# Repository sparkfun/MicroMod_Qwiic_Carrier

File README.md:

SparkFun MicroMod Qwiic Carrier Board
========================================

<table class="table table-hover table-striped table-bordered">
    <tr align="center">
      <td></td>
      <td></td>
    </tr>
    <tr align="center">
      <td><a href="https://www.sparkfun.com/products/17723">SparkFun Qwiic Carrier - Single</a></td>
      <td><a href="https://www.sparkfun.com/products/17724">SparkFun Qwiic Carrier - Double</a></td>
    </tr>
</table>

The MicroMod Qwiic Carrier Board for the [SparkFun MicroMod Ecosystem](https://www.sparkfun.com/micromod) can be used to rapidly prototype with other Qwiic devices. The MicroMod M.2 socket provides users the freedom to experiment with any processor board in the MicroMod ecosystem. This board also features two Qwiic connectors and 4-40 screw inserts to connect and mount Qwiic devices.

Repository Contents
-------------------
* **/Hardware** - Eagle design files (.brd, .sch)

Documentation
--------------
* **[Hookup Guide](https://learn.sparkfun.com/tutorials/1596)** - Basic hookup guide for the MicroMod Qwiic Carrier Board.

Product Versions
----------------
* [DEV-17723](https://www.sparkfun.com/products/17723) - Single
* [DEV-17724](https://www.sparkfun.com/products/17724) - Double

License Information
-------------------

This product is _**open source**_! 

Please review the LICENSE.md file for license information. 

If you have any questions or concerns on licensing, please contact technical support on our [SparkFun forums](https://forum.sparkfun.com/viewforum.php?f=152).

Distributed as-is; no warranty is given.

- Your friends at SparkFun.

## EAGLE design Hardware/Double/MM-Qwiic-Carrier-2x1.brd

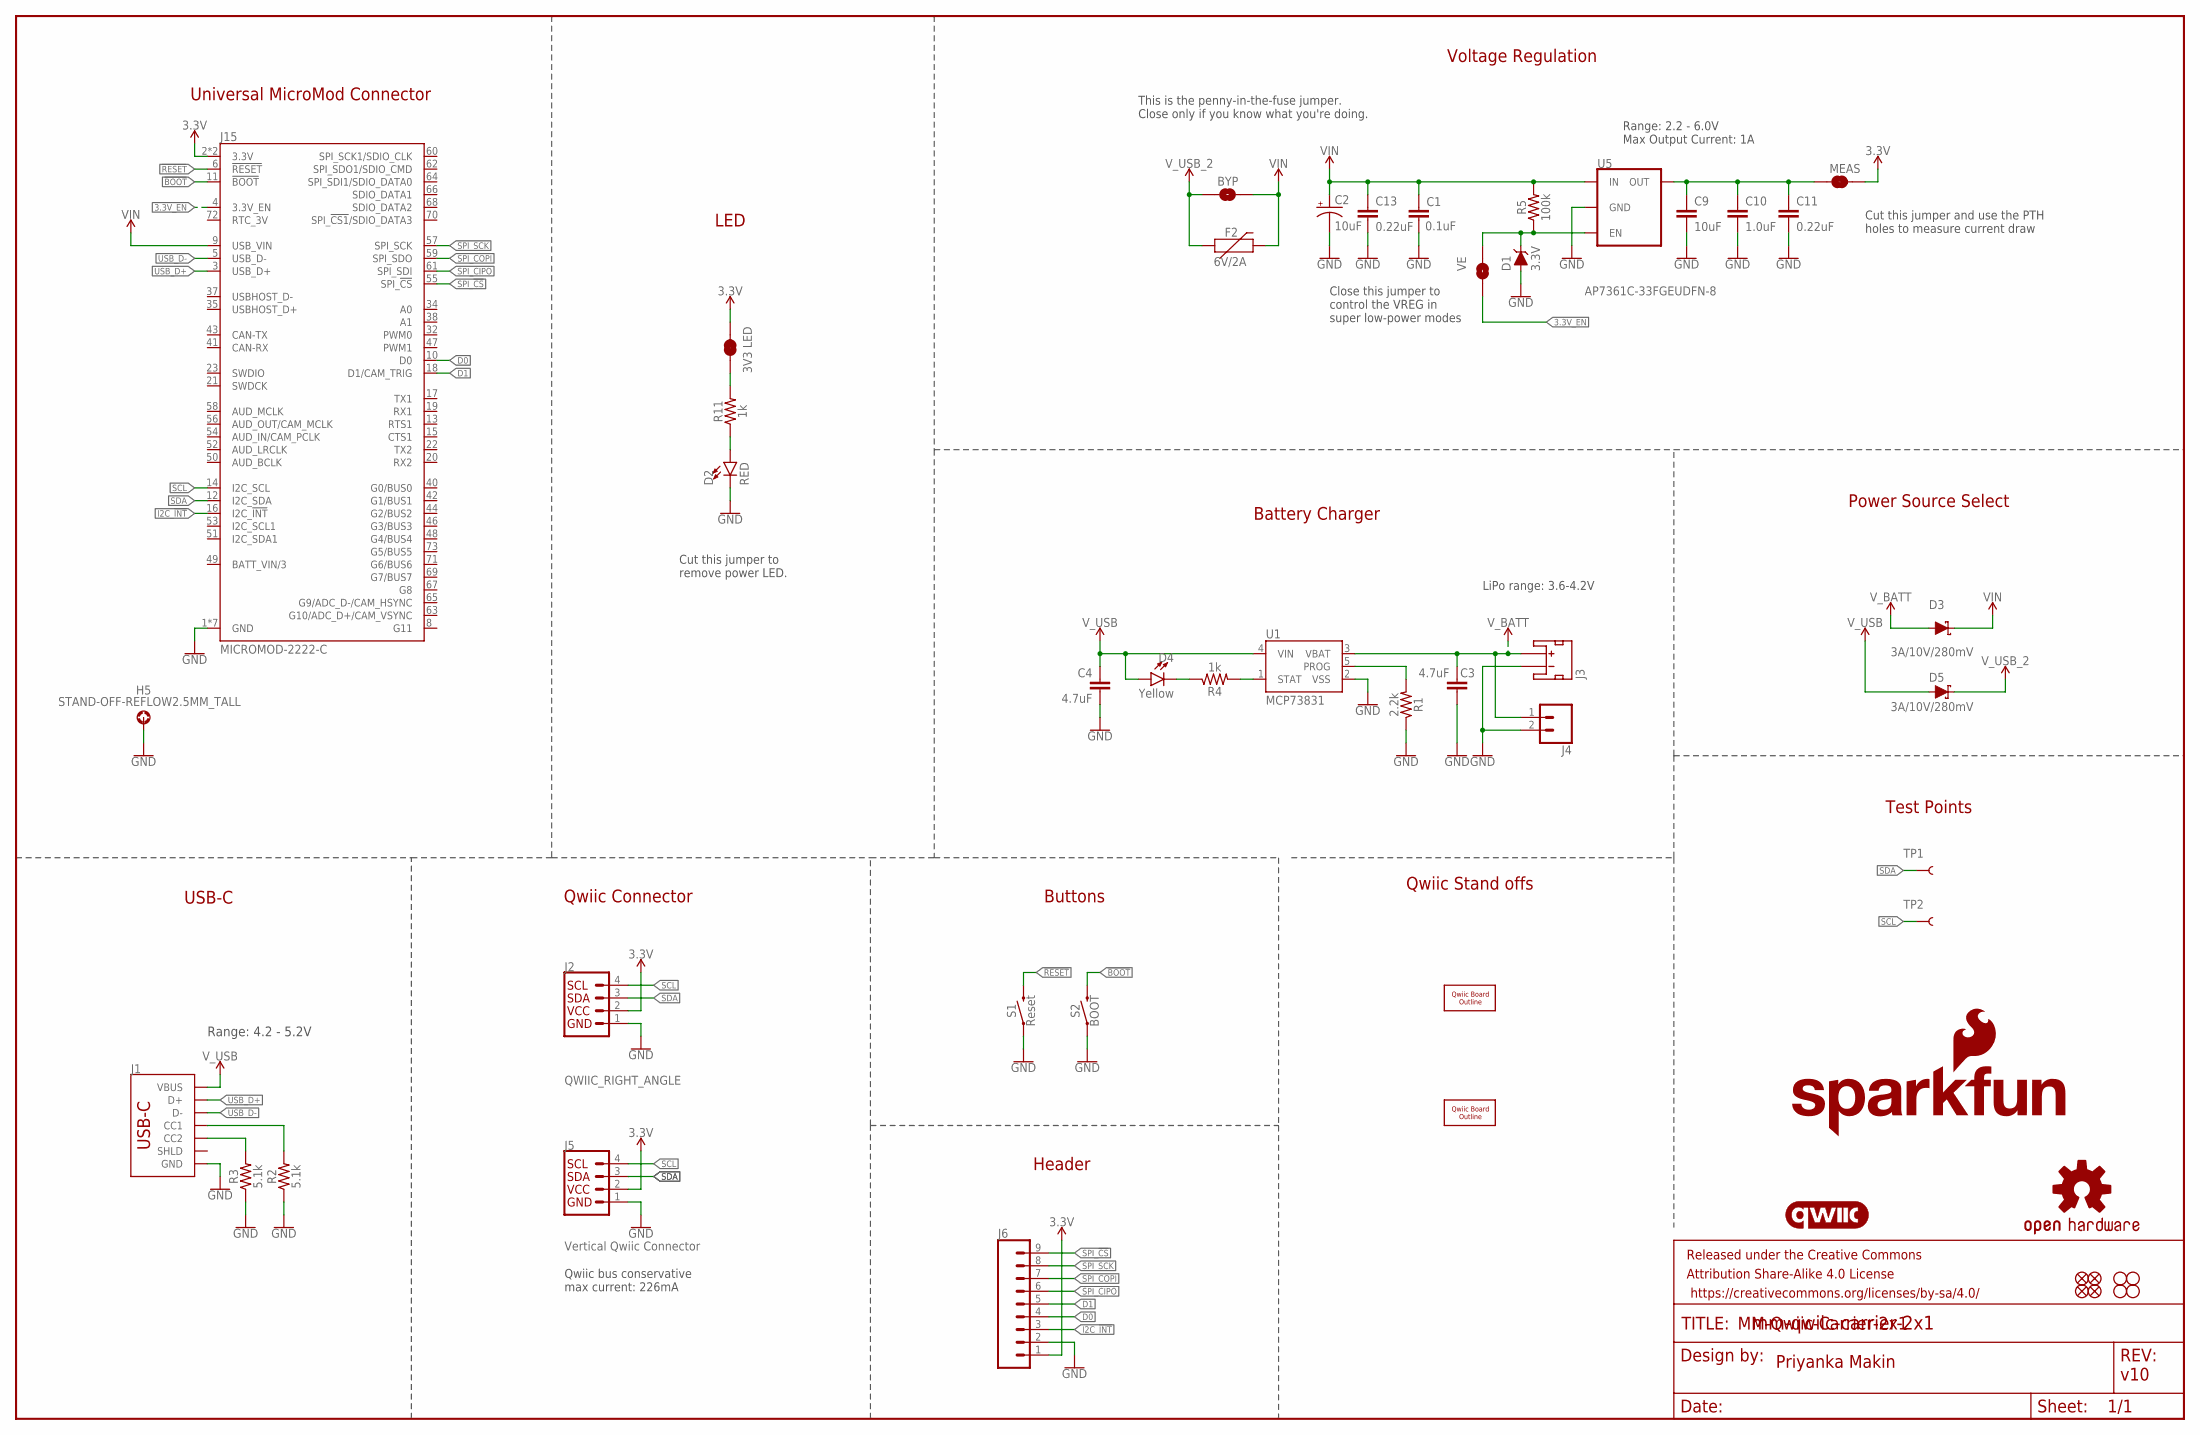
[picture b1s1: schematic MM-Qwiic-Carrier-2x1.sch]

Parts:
BYP: JUMPER-SMT_2_NO_SILK; SMT-JUMPER_2_NO_SILK
C1: 0.1uF; 0603
C2: 10uF; EIA3216
C3, C4: 4.7uF; 0603
C9: 10uF; 0603
C10: 1.0uF; 0603
C11, C13: 0.22uF; 0603
D1: 3.3V; SOD-323
D2: RED; LED-0603
D3, D5: 3A/10V/280mV; SOD-323
D4: Yellow; LED-0603
F2: 6V/2A; 1210
FD1, FD2, FD3, FD4: FIDUCIALUFIDUCIAL; FIDUCIAL-MICRO
FRAME1: FRAME-LEDGER; CREATIVE_COMMONS
H1, H2, H3, H4: STAND-OFF
H5: STAND-OFF-REFLOW2.5MM_TALL; STAND-OFF-REFLOW-M2.5
J1: USB_C_2-LAYER_PADS; USB-C-16P-2LAYER-PADS
J2: QWIIC_RIGHT_ANGLE; JST04_1MM_RA
J3: JST_2MM_MALE; JST-2-SMD
J4: CONN_021X02_NO_SILK; 1X02_NO_SILK
J5: Vertical Qwiic Connector; JST04_1MM_VERT
J6: CONN_09NO_SILK; 1X09_NO_SILK
J15: MICROMOD-2222-C; M.2-CONNECTOR-E
JP4: 3V3 LED; SMT-JUMPER_2_NC_TRACE_SILK
JP6: VE; SMT-JUMPER_2_NO_SILK
LOGO1: SFE_LOGO_NAME_FLAME.2_INCH; SFE_LOGO_NAME_FLAME_.2
LOGO2: QWIIC_LOGO_CONNECTOR; QWIIC_5.5MM
LOGO3: OSHW-LOGOM; OSHW-LOGO-M
MEAS: JUMPER-COMBO_2_NC_TRACE; COMBO-JUMPER_2_NC_TRACE
R1: 2.2k; 0603
R2, R3: 5.1k; 0603
R4, R11: 1k; 0603
R5: 100k; 0603
S1: Reset; TACTILE_SWITCH_SMD_5.2MM
S2: BOOT; TACTILE_SWITCH_SMD_5.2MM
TP1, TP2: TEST-POINT3X5; PAD.03X.05
U1: MCP73831; SOT23-5
U5: AP7361C-33FGEUDFN-8; UDFN-8
U$2, U$5: QWIIC_BOARD_OUTLINESTANDOFF; QWIIC_BOARD_MOUNT_SMD_STANDOFFS

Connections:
3.3V: J2.2, J5.2, J6.1, J15.2 (3.3V), J15.74 (3.3V), JP4.2, MEAS.2, MEAS.4 (2)
3.3V_EN: J15.4 (3.3V_EN), JP6.1
!BOOT!: J15.11 (!BOOT!), S2.3 (2), S2.4 (2)
!RESET!: J15.6 (!RESET!), S1.3 (2), S1.4 (2)
D0: J6.4, J15.10 (D0)
D1: J6.5, J15.18 (D1/CAM_TRIG)
GND: C1.2, C2.-, C3.2, C4.2, C9.2, C10.2, C11.2, C13.2, D1.A, D2.C, H5.1, J1.GND, J1.GND2 (GND), J2.1, J3.1 (-), J4.2, J5.1, J6.2, J15.1 (GND), J15.7 (GND), J15.33 (GND), J15.36 (GND), J15.39 (GND), J15.45 (GND), J15.75 (GND), R1.1, R2.1, R3.1, S1.1, S1.2 (1), S2.1, S2.2 (1), U1.2 (VSS), U5.4 (GND), U5.EP (GND)
I2C_!INT!: J6.3, J15.16 (I2C_!INT!)
unnamed: C9.1, C10.1, C11.1, MEAS.1, MEAS.3 (1), U5.1 (OUT)
unnamed: R1.2, U1.5 (PROG)
unnamed: D4.C, R4.1
unnamed: JP4.1, R11.2
unnamed: D2.A, R11.1
unnamed: R4.2, U1.1 (STAT)
unnamed: J1.A5 (CC1), R2.2
unnamed: J1.B5 (CC2), R3.2
SCL: J2.4, J5.4, J15.14 (I2C_SCL), TP2.P$1
SDA: J2.3, J5.3, J15.12 (I2C_SDA), TP1.P$1
SPI_!CS!: J6.9, J15.55 (SPI_!CS!)
SPI_CIPO: J6.6, J15.61 (SPI_SDI)
SPI_COPI: J6.7, J15.59 (SPI_SDO)
SPI_SCK: J6.8, J15.57 (SPI_SCK)
USB_D+: J1.A6 (D+), J1.B6 (D+), J15.3 (USB_D+)
USB_D-: J1.A7 (D-), J1.B7 (D-), J15.5 (USB_D-)
VIN: BYP.2, C1.1, C2.+, C13.1, D3.C, F2.2, J15.9 (USB_VIN), R5.2, U5.8 (IN)
VREG_EN: D1.C, JP6.2, R5.1, U5.5 (EN)
V_BATT: C3.1, D3.A, J3.2 (+), J4.1, U1.3 (VBAT)
V_USB: C4.1, D4.A, D5.A, J1.VBUS1 (VBUS), J1.VBUS2 (VBUS), U1.4 (VIN)
V_USB_2: BYP.1, D5.C, F2.1

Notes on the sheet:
USB-C
Universal MicroMod Connector
Priyanka Makin
MM-Qwiic-Carrier-2x1
LED
v10
Cut this jumper to remove power LED.
Range: 4.2 - 5.2V
Voltage Regulation
Range: 2.2 - 6.0V Max Output Current: 1A
Close this jumper to control the VREG in super low-power modes
This is the penny-in-the-fuse jumper. Close only if you know what you're doing.
Qwiic Connector
Buttons
Battery Charger
Qwiic Stand offs
Power Source Select
Test Points
Qwiic bus conservative max current: 226mA
Header
Cut this jumper and use the PTH holes to measure current draw
LiPo range: 3.6-4.2V

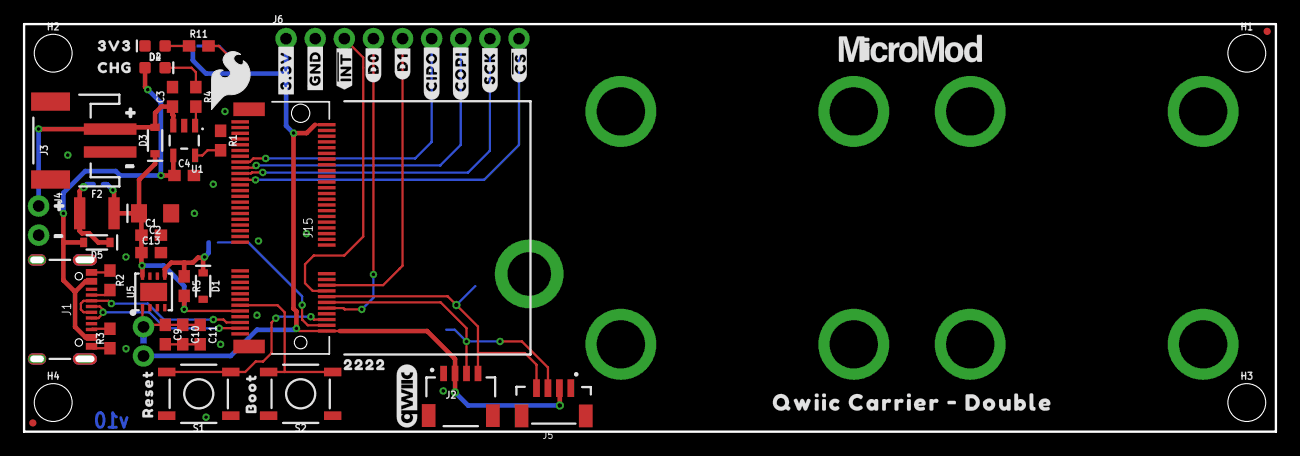
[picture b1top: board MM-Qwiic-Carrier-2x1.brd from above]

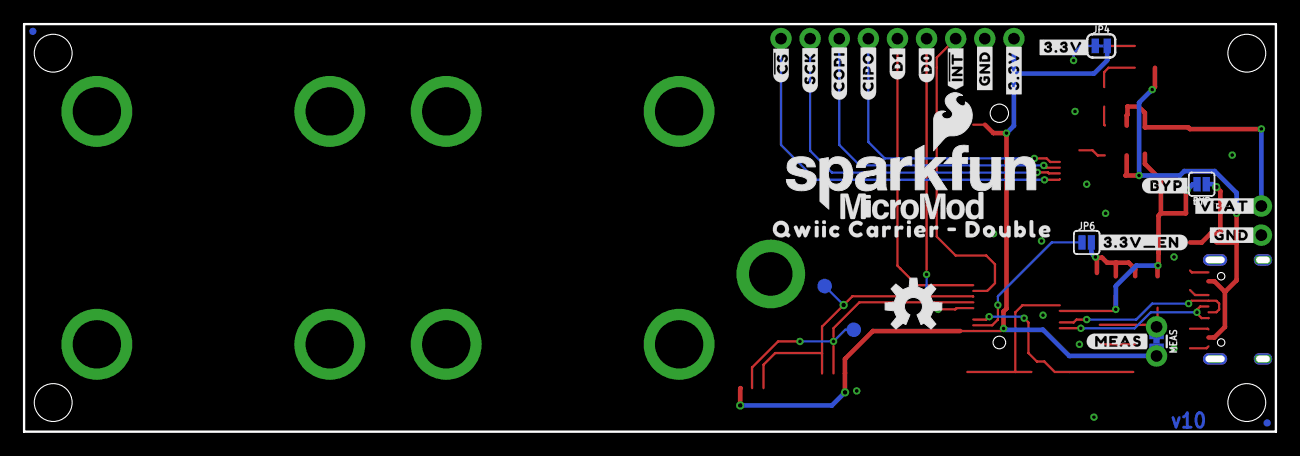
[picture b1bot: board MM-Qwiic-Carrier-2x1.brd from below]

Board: 2 copper layers, 109.2 x 35.6 mm, 90 parts (27 on the bottom side), 29 nets.

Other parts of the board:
U$1: #3#3V_EN#0
U$3: 3V30
U$4: CHG0
U$6, U$35, U$38: #3#3V#0
U$7: #BYP#0
U$8, U$14, U$33: #GND#0
U$9: #MEAS#0
U$10, U$13: QWIIC_CARRIER_#_DOUBLE0
U$11, U$32, U$36, U$37: #0
U$12: #VBAT#0
U$15, U$16: ##INT##0
U$17, U$18: #D0#0
U$20, U$21: #D1#0
U$22, U$23: #CIPO#0
U$24, U$25: #COPI#0
U$26, U$27: #SCK#0
U$28, U$29: ##CS##0
U$30: RESET0
U$31: BOOT0
U$34: 22220
U$44: SFE_LOGO_FLAME_.2
U$67, U$68: MICROMOD_LOGO_.5

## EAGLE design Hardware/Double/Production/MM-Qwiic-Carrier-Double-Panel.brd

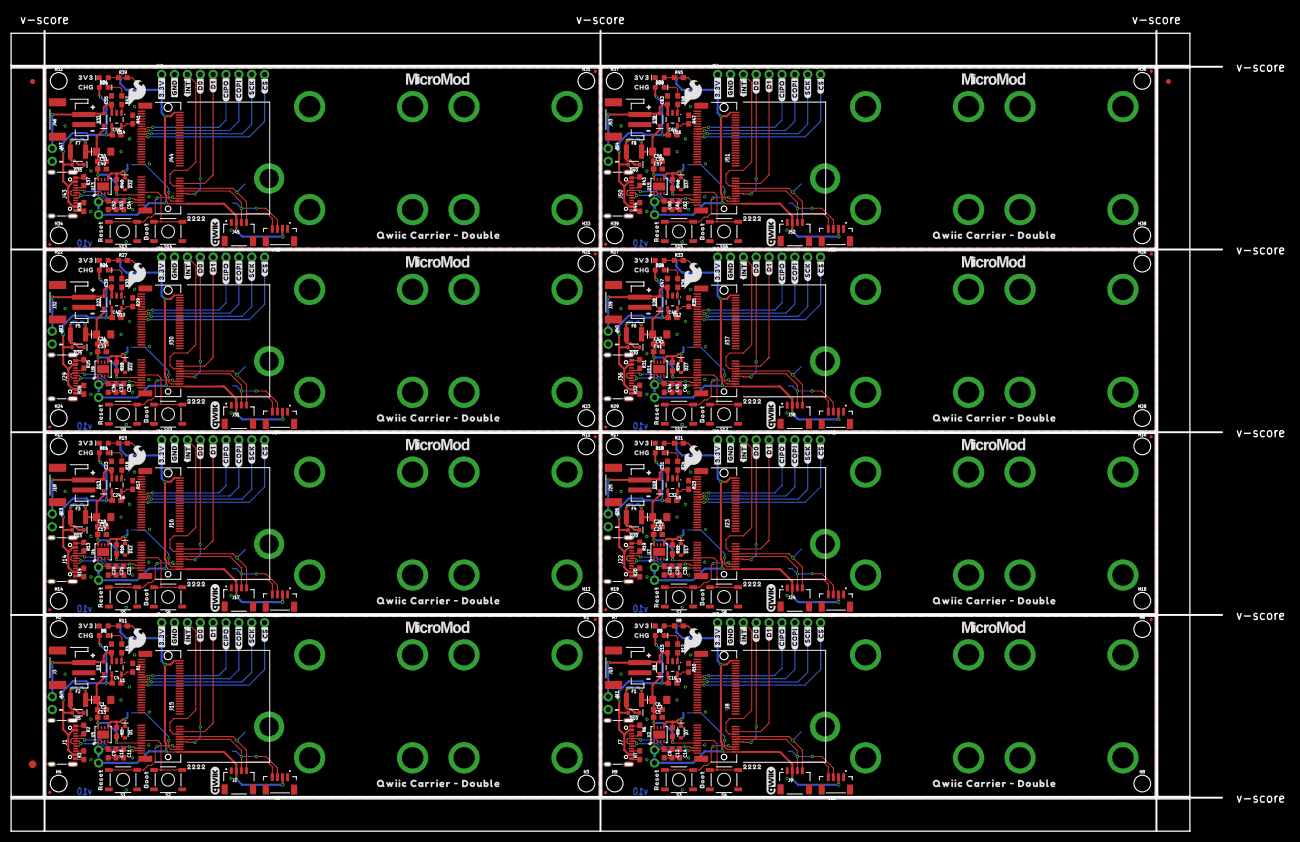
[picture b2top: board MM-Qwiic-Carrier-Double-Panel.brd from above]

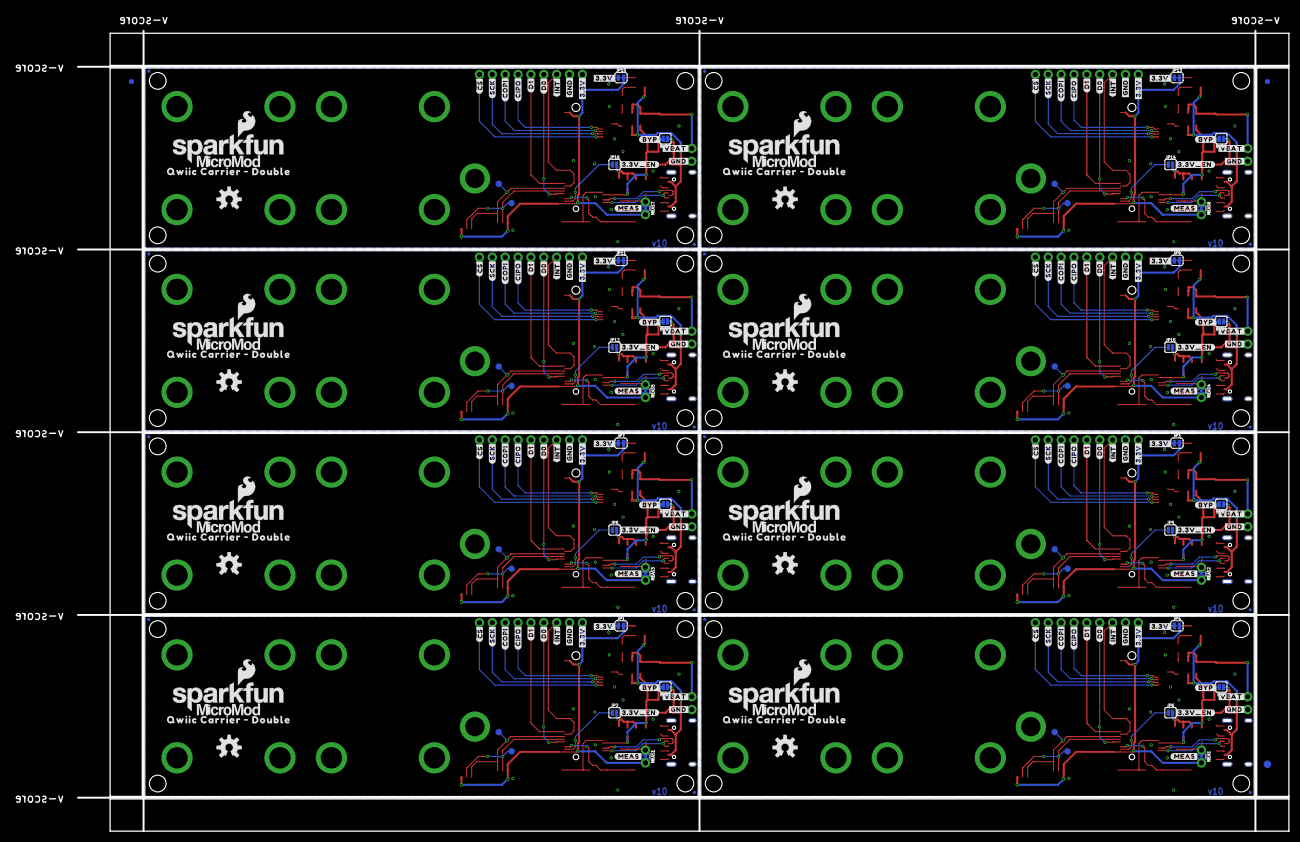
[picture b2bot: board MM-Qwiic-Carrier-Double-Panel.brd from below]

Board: 2 copper layers, 239.0 x 158.0 mm, 718 parts (219 on the bottom side), 232 nets.

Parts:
BYP, BYP1, BYP2, BYP3, BYP4, BYP5, BYP6, BYP7: JUMPER-SMT_2_NO_SILK; SMT-JUMPER_2_NO_SILK
C1, C6, C18, C26, C34, C42, C50, C58: 0.1uF; 0603
C2, C7, C19, C27, C35, C43, C51, C59: 10uF; EIA3216
C3, C4, C15, C16, C23, C24, C31, C32, C39, C40, C47, C48, C55, C56, C63, C64: 4.7uF; 0603
C5, C11, C13, C14, C17, C22, C25, C30, C33, C38, C41, C46, C49, C54, C57, C62: 0.22uF; 0603
C8, C9, C20, C28, C36, C44, C52, C60: 10uF; 0603
C10, C12, C21, C29, C37, C45, C53, C61: 1.0uF; 0603
D1, D7, D12, D17, D22, D27, D32, D37: 3.3V; SOD-323
D2, D6, D11, D16, D21, D26, D31, D36: RED; LED-0603
D3, D5, D8, D10, D13, D15, D18, D20, D23, D25, D28, D30, D33, D35, D38, D40: 3A/10V/280mV; SOD-323
D4, D9, D14, D19, D24, D29, D34, D39: Yellow; LED-0603
E$1, E$2, E$3, E$4: FIDUCIAL-1X2
E$5, E$6: FIDUCIAL-1.5X3
F1, F2, F3, F4, F5, F6, F7, F8: 6V/2A; 1210
FD1, FD2, FD3, FD4, FD5, FD6, FD7, FD8, FD9, FD10, FD11, FD12, FD13, FD14, FD15, FD16, FD17, FD18, FD19, FD20, FD21, FD22, FD23, FD24, FD25, FD26, FD27, FD28, FD29, FD30, FD31, FD32: FIDUCIALUFIDUCIAL; FIDUCIAL-MICRO
H1, H2, H3, H4, H6, H7, H8, H9, H11, H12, H13, H14, H16, H17, H18, H19, H21, H22, H23, H24, H26, H27, H28, H29, H31, H32, H33, H34, H36, H37, H38, H39: STAND-OFF
H5, H10, H15, H20, H25, H30, H35, H40: STAND-OFF-REFLOW2.5MM_TALL; STAND-OFF-REFLOW-M2.5
J1, J7, J14, J22, J29, J36, J43, J50: USB-C-16P-2LAYER-PADS
J2, J9, J17, J24, J31, J38, J45, J52: QWIIC_RIGHT_ANGLE; JST04_1MM_RA
J3, J10, J18, J25, J32, J39, J46, J53: JST-2-SMD
J4, J11, J19, J26, J33, J40, J47, J54: 1X02_NO_SILK
J5, J12, J20, J27, J34, J41, J48, J55: Vertical Qwiic Connector; JST04_1MM_VERT
J6, J13, J21, J28, J35, J42, J49, J56: 1X09_NO_SILK
J8, J15, J16, J23, J30, J37, J44, J51: MICROMOD-2222-C; M.2-CONNECTOR-E
JP1, JP3, JP4, JP7, JP9, JP11, JP13, JP15: 3V3 LED; SMT-JUMPER_2_NC_TRACE_SILK
JP2, JP5, JP6, JP8, JP10, JP12, JP14, JP16: VE; SMT-JUMPER_2_NO_SILK
LOGO1, LOGO6, LOGO9, LOGO12, LOGO15, LOGO18, LOGO21, LOGO24: SFE_LOGO_NAME_FLAME.2_INCH; SFE_LOGO_NAME_FLAME_.2
LOGO2, LOGO4, LOGO7, LOGO10, LOGO13, LOGO16, LOGO19, LOGO22: QWIIC_LOGO_CONNECTOR; QWIIC_5.5MM
LOGO3, LOGO5, LOGO8, LOGO11, LOGO14, LOGO17, LOGO20, LOGO23: OSHW-LOGOM; OSHW-LOGO-M
MEAS, MEAS1, MEAS2, MEAS3, MEAS4, MEAS5, MEAS6, MEAS7: COMBO-JUMPER_2_NC_TRACE
R1, R10, R17, R23, R29, R35, R41, R47: 2.2k; 0603
R2, R3, R6, R7, R13, R14, R19, R20, R25, R26, R31, R32, R37, R38, R43, R44: 5.1k; 0603
R4, R8, R11, R12, R15, R18, R21, R24, R27, R30, R33, R36, R39, R42, R45, R48: 1k; 0603
R5, R9, R16, R22, R28, R34, R40, R46: 100k; 0603
S1, S3, S5, S7, S9, S11, S13, S15: Reset; TACTILE_SWITCH_SMD_5.2MM
S2, S4, S6, S8, S10, S12, S14, S16: BOOT; TACTILE_SWITCH_SMD_5.2MM
TP1, TP2, TP3, TP4, TP5, TP6, TP7, TP8, TP9, TP10, TP11, TP12, TP13, TP14, TP15, TP16: TEST-POINT3X5; PAD.03X.05
U1, U3, U6, U8, U10, U12, U14, U16: MCP73831; SOT23-5
U2, U4, U5, U7, U9, U11, U13, U15: AP7361C-33FGEUDFN-8; UDFN-8
U$1, U$48, U$90, U$130, U$170, U$210, U$250, U$290: #3#3V_EN#0
U$2, U$5, U$46, U$78, U$88, U$118, U$128, U$158, U$168, U$198, U$208, U$238, U$248, U$278, U$288, U$318: QWIIC_BOARD_OUTLINESTANDOFF; QWIIC_BOARD_MOUNT_SMD_STANDOFFS
U$3, U$47, U$89, U$129, U$169, U$209, U$249, U$289: 3V30
U$4, U$41, U$84, U$124, U$164, U$204, U$244, U$284: CHG0
U$6, U$35, U$38, U$42, U$72, U$73, U$85, U$112, U$113, U$125, U$152, U$153, U$165, U$192, U$193, U$205, U$232, U$233, U$245, U$272, U$273, U$285, U$312, U$313: #3#3V#0
U$7, U$43, U$86, U$126, U$166, U$206, U$246, U$286: #BYP#0
U$8, U$14, U$33, U$49, U$50, U$58, U$91, U$92, U$100, U$131, U$132, U$140, U$171, U$172, U$180, U$211, U$212, U$220, U$251, U$252, U$260, U$291, U$292, U$300: #GND#0
U$9, U$45, U$87, U$127, U$167, U$207, U$247, U$287: #MEAS#0
U$10, U$13, U$79, U$80, U$119, U$120, U$159, U$160, U$199, U$200, U$239, U$240, U$279, U$280, U$319, U$320: QWIIC_CARRIER_#_DOUBLE0
U$11, U$32, U$36, U$37, U$59, U$60, U$61, U$62, U$101, U$102, U$103, U$104, U$141, U$142, U$143, U$144, U$181, U$182, U$183, U$184, U$221, U$222, U$223, U$224, U$261, U$262, U$263, U$264, U$301, U$302, U$303, U$304: #0
U$12, U$57, U$99, U$139, U$179, U$219, U$259, U$299: #VBAT#0
U$15, U$16, U$76, U$77, U$116, U$117, U$156, U$157, U$196, U$197, U$236, U$237, U$276, U$277, U$316, U$317: ##INT##0
U$17, U$18, U$63, U$64, U$105, U$106, U$145, U$146, U$185, U$186, U$225, U$226, U$265, U$266, U$305, U$306: #D0#0
U$19, U$44, U$81, U$121, U$161, U$201, U$241, U$281: SFE_LOGO_FLAME_.2
U$20, U$21, U$65, U$66, U$107, U$108, U$147, U$148, U$187, U$188, U$227, U$228, U$267, U$268, U$307, U$308: #D1#0
U$22, U$23, U$51, U$52, U$93, U$94, U$133, U$134, U$173, U$174, U$213, U$214, U$253, U$254, U$293, U$294: #CIPO#0
U$24, U$25, U$53, U$54, U$95, U$96, U$135, U$136, U$175, U$176, U$215, U$216, U$255, U$256, U$295, U$296: #COPI#0
U$26, U$27, U$55, U$56, U$97, U$98, U$137, U$138, U$177, U$178, U$217, U$218, U$257, U$258, U$297, U$298: #SCK#0
U$28, U$29, U$74, U$75, U$114, U$115, U$154, U$155, U$194, U$195, U$234, U$235, U$274, U$275, U$314, U$315: ##CS##0
U$30, U$69, U$109, U$149, U$189, U$229, U$269, U$309: RESET0
U$31, U$70, U$110, U$150, U$190, U$230, U$270, U$310: BOOT0
U$34, U$71, U$111, U$151, U$191, U$231, U$271, U$311: 22220
U$39, U$40, U$67, U$68, U$82, U$83, U$122, U$123, U$162, U$163, U$202, U$203, U$242, U$243, U$282, U$283: MICROMOD_LOGO_.5

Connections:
3.3V: J2.2, J5.2, J6.1, J15.2, J15.74, JP4.2, MEAS.2, MEAS.4
3.3V1: J8.2, J8.74, J9.2, J12.2, J13.1, JP1.2, MEAS1.2, MEAS1.4
3.3V2: J16.2, J16.74, J17.2, J20.2, J21.1, JP3.2, MEAS2.2, MEAS2.4
3.3V3: J23.2, J23.74, J24.2, J27.2, J28.1, JP7.2, MEAS3.2, MEAS3.4
3.3V4: J30.2, J30.74, J31.2, J34.2, J35.1, JP9.2, MEAS4.2, MEAS4.4
3.3V5: J37.2, J37.74, J38.2, J41.2, J42.1, JP11.2, MEAS5.2, MEAS5.4
3.3V6: J44.2, J44.74, J45.2, J48.2, J49.1, JP13.2, MEAS6.2, MEAS6.4
3.3V7: J51.2, J51.74, J52.2, J55.2, J56.1, JP15.2, MEAS7.2, MEAS7.4
3.3V_EN: J15.4, JP6.1
3.3V_EN1: J8.4, JP2.1
3.3V_EN2: J16.4, JP5.1
3.3V_EN3: J23.4, JP8.1
3.3V_EN4: J30.4, JP10.1
3.3V_EN5: J37.4, JP12.1
3.3V_EN6: J44.4, JP14.1
3.3V_EN7: J51.4, JP16.1
!BOOT!: J15.11, S2.3, S2.4
!BOOT!1: J8.11, S4.3, S4.4
!BOOT!2: J16.11, S6.3, S6.4
!BOOT!3: J23.11, S8.3, S8.4
!BOOT!4: J30.11, S10.3, S10.4
!BOOT!5: J37.11, S12.3, S12.4
!BOOT!6: J44.11, S14.3, S14.4
!BOOT!7: J51.11, S16.3, S16.4
!RESET!: J15.6, S1.3, S1.4
!RESET!1: J8.6, S3.3, S3.4
!RESET!2: J16.6, S5.3, S5.4
!RESET!3: J23.6, S7.3, S7.4
!RESET!4: J30.6, S9.3, S9.4
!RESET!5: J37.6, S11.3, S11.4
!RESET!6: J44.6, S13.3, S13.4
!RESET!7: J51.6, S15.3, S15.4
D0: J6.4, J15.10
D1: J6.5, J15.18
D2: J8.10, J13.4
D3: J8.18, J13.5
D4: J16.10, J21.4
D5: J16.18, J21.5
D6: J23.10, J28.4
D7: J23.18, J28.5
D8: J30.10, J35.4
D9: J30.18, J35.5
D10: J37.10, J42.4
D11: J37.18, J42.5
D12: J44.10, J49.4
D13: J44.18, J49.5
D14: J51.10, J56.4
D15: J51.18, J56.5
GND: C1.2, C2.-, C3.2, C4.2, C9.2, C10.2, C11.2, C13.2, D1.A, D2.C, H5.1, J1.GND, J1.GND2, J2.1, J3.1, J4.2, J5.1, J6.2, J15.1, J15.7, J15.33, J15.36, J15.39, J15.45, J15.75, R1.1, R2.1, R3.1, S1.1, S1.2, S2.1, S2.2, U1.2, U5.4, U5.EP
GND1: C5.2, C6.2, C7.-, C8.2, C12.2, C14.2, C15.2, C16.2, D6.C, D7.A, H10.1, J7.GND, J7.GND2, J8.1, J8.7, J8.33, J8.36, J8.39, J8.45, J8.75, J9.1, J10.1, J11.2, J12.1, J13.2, R6.1, R7.1, R10.1, S3.1, S3.2, S4.1, S4.2, U2.4, U2.EP, U3.2
GND2: C17.2, C18.2, C19.-, C20.2, C21.2, C22.2, C23.2, C24.2, D11.C, D12.A, H15.1, J14.GND, J14.GND2, J16.1, J16.7, J16.33, J16.36, J16.39, J16.45, J16.75, J17.1, J18.1, J19.2, J20.1, J21.2, R13.1, R14.1, R17.1, S5.1, S5.2, S6.1, S6.2, U4.4, U4.EP, U6.2
GND3: C25.2, C26.2, C27.-, C28.2, C29.2, C30.2, C31.2, C32.2, D16.C, D17.A, H20.1, J22.GND, J22.GND2, J23.1, J23.7, J23.33, J23.36, J23.39, J23.45, J23.75, J24.1, J25.1, J26.2, J27.1, J28.2, R19.1, R20.1, R23.1, S7.1, S7.2, S8.1, S8.2, U7.4, U7.EP, U8.2
GND4: C33.2, C34.2, C35.-, C36.2, C37.2, C38.2, C39.2, C40.2, D21.C, D22.A, H25.1, J29.GND, J29.GND2, J30.1, J30.7, J30.33, J30.36, J30.39, J30.45, J30.75, J31.1, J32.1, J33.2, J34.1, J35.2, R25.1, R26.1, R29.1, S9.1, S9.2, S10.1, S10.2, U9.4, U9.EP, U10.2
GND5: C41.2, C42.2, C43.-, C44.2, C45.2, C46.2, C47.2, C48.2, D26.C, D27.A, H30.1, J36.GND, J36.GND2, J37.1, J37.7, J37.33, J37.36, J37.39, J37.45, J37.75, J38.1, J39.1, J40.2, J41.1, J42.2, R31.1, R32.1, R35.1, S11.1, S11.2, S12.1, S12.2, U11.4, U11.EP, U12.2
GND6: C49.2, C50.2, C51.-, C52.2, C53.2, C54.2, C55.2, C56.2, D31.C, D32.A, H35.1, J43.GND, J43.GND2, J44.1, J44.7, J44.33, J44.36, J44.39, J44.45, J44.75, J45.1, J46.1, J47.2, J48.1, J49.2, R37.1, R38.1, R41.1, S13.1, S13.2, S14.1, S14.2, U13.4, U13.EP, U14.2
GND7: C57.2, C58.2, C59.-, C60.2, C61.2, C62.2, C63.2, C64.2, D36.C, D37.A, H40.1, J50.GND, J50.GND2, J51.1, J51.7, J51.33, J51.36, J51.39, J51.45, J51.75, J52.1, J53.1, J54.2, J55.1, J56.2, R43.1, R44.1, R47.1, S15.1, S15.2, S16.1, S16.2, U15.4, U15.EP, U16.2
I2C_!INT!: J6.3, J15.16
I2C_!INT!1: J8.16, J13.3
I2C_!INT!2: J16.16, J21.3
I2C_!INT!3: J23.16, J28.3
I2C_!INT!4: J30.16, J35.3
I2C_!INT!5: J37.16, J42.3
I2C_!INT!6: J44.16, J49.3
I2C_!INT!7: J51.16, J56.3
unnamed: C9.1, C10.1, C11.1, MEAS.1, MEAS.3, U5.1
unnamed: R1.2, U1.5
unnamed: D4.C, R4.1
unnamed: JP4.1, R11.2
unnamed: J7.A5, R6.2
unnamed: D2.A, R11.1
unnamed: J7.B5, R7.2
unnamed: R4.2, U1.1
unnamed: JP1.1, R8.2
unnamed: J1.A5, R2.2
unnamed: J1.B5, R3.2
unnamed: D6.A, R8.1
unnamed: C8.1, C12.1, C14.1, MEAS1.1, MEAS1.3, U2.1
unnamed: R10.2, U3.5
unnamed: D9.C, R12.1
unnamed: R12.2, U3.1
unnamed: J14.A5, R13.2
unnamed: J14.B5, R14.2
unnamed: JP3.1, R15.2
unnamed: D11.A, R15.1
unnamed: C20.1, C21.1, C22.1, MEAS2.1, MEAS2.3, U4.1
unnamed: R17.2, U6.5
unnamed: D14.C, R18.1
unnamed: R18.2, U6.1
unnamed: J22.A5, R19.2
unnamed: J22.B5, R20.2
unnamed: JP7.1, R21.2
unnamed: D16.A, R21.1
unnamed: C28.1, C29.1, C30.1, MEAS3.1, MEAS3.3, U7.1
unnamed: R23.2, U8.5
unnamed: D19.C, R24.1
unnamed: R24.2, U8.1
unnamed: J29.A5, R25.2
unnamed: J29.B5, R26.2
unnamed: JP9.1, R27.2
unnamed: D21.A, R27.1
unnamed: C36.1, C37.1, C38.1, MEAS4.1, MEAS4.3, U9.1
unnamed: R29.2, U10.5
unnamed: D24.C, R30.1
unnamed: R30.2, U10.1
unnamed: J36.A5, R31.2
unnamed: J36.B5, R32.2
unnamed: JP11.1, R33.2
unnamed: D26.A, R33.1
unnamed: C44.1, C45.1, C46.1, MEAS5.1, MEAS5.3, U11.1
unnamed: R35.2, U12.5
unnamed: D29.C, R36.1
unnamed: R36.2, U12.1
unnamed: J43.A5, R37.2
unnamed: J43.B5, R38.2
unnamed: JP13.1, R39.2
unnamed: D31.A, R39.1
unnamed: C52.1, C53.1, C54.1, MEAS6.1, MEAS6.3, U13.1
unnamed: R41.2, U14.5
unnamed: D34.C, R42.1
unnamed: R42.2, U14.1
unnamed: J50.A5, R43.2
unnamed: J50.B5, R44.2
unnamed: JP15.1, R45.2
unnamed: D36.A, R45.1
unnamed: C60.1, C61.1, C62.1, MEAS7.1, MEAS7.3, U15.1
unnamed: R47.2, U16.5
unnamed: D39.C, R48.1
unnamed: R48.2, U16.1
SCL: J2.4, J5.4, J15.14, TP2.P$1
SCL1: J8.14, J9.4, J12.4, TP4.P$1
SCL2: J16.14, J17.4, J20.4, TP6.P$1
SCL3: J23.14, J24.4, J27.4, TP8.P$1
SCL4: J30.14, J31.4, J34.4, TP10.P$1
SCL5: J37.14, J38.4, J41.4, TP12.P$1
SCL6: J44.14, J45.4, J48.4, TP14.P$1
SCL7: J51.14, J52.4, J55.4, TP16.P$1
SDA: J2.3, J5.3, J15.12, TP1.P$1
SDA1: J8.12, J9.3, J12.3, TP3.P$1
SDA2: J16.12, J17.3, J20.3, TP5.P$1
SDA3: J23.12, J24.3, J27.3, TP7.P$1
SDA4: J30.12, J31.3, J34.3, TP9.P$1
SDA5: J37.12, J38.3, J41.3, TP11.P$1
SDA6: J44.12, J45.3, J48.3, TP13.P$1
SDA7: J51.12, J52.3, J55.3, TP15.P$1
SPI_!CS!: J6.9, J15.55
SPI_!CS!1: J8.55, J13.9
SPI_!CS!2: J16.55, J21.9
SPI_!CS!3: J23.55, J28.9
SPI_!CS!4: J30.55, J35.9
SPI_!CS!5: J37.55, J42.9
SPI_!CS!6: J44.55, J49.9
SPI_!CS!7: J51.55, J56.9
SPI_CIPO: J6.6, J15.61
SPI_CIPO1: J8.61, J13.6
SPI_CIPO2: J16.61, J21.6
SPI_CIPO3: J23.61, J28.6
SPI_CIPO4: J30.61, J35.6
SPI_CIPO5: J37.61, J42.6
SPI_CIPO6: J44.61, J49.6
SPI_CIPO7: J51.61, J56.6
SPI_COPI: J6.7, J15.59
SPI_COPI1: J8.59, J13.7
SPI_COPI2: J16.59, J21.7
SPI_COPI3: J23.59, J28.7
SPI_COPI4: J30.59, J35.7
SPI_COPI5: J37.59, J42.7
SPI_COPI6: J44.59, J49.7
SPI_COPI7: J51.59, J56.7
SPI_SCK: J6.8, J15.57
SPI_SCK1: J8.57, J13.8
SPI_SCK2: J16.57, J21.8
SPI_SCK3: J23.57, J28.8
SPI_SCK4: J30.57, J35.8
SPI_SCK5: J37.57, J42.8
SPI_SCK6: J44.57, J49.8
SPI_SCK7: J51.57, J56.8
USB_D+: J1.A6, J1.B6, J15.3
USB_D+1: J7.A6, J7.B6, J8.3
USB_D+2: J14.A6, J14.B6, J16.3
USB_D+3: J22.A6, J22.B6, J23.3
USB_D+4: J29.A6, J29.B6, J30.3
USB_D+5: J36.A6, J36.B6, J37.3
USB_D+6: J43.A6, J43.B6, J44.3
USB_D+7: J50.A6, J50.B6, J51.3
USB_D-: J1.A7, J1.B7, J15.5
USB_D-1: J7.A7, J7.B7, J8.5
USB_D-2: J14.A7, J14.B7, J16.5
USB_D-3: J22.A7, J22.B7, J23.5
USB_D-4: J29.A7, J29.B7, J30.5
USB_D-5: J36.A7, J36.B7, J37.5
USB_D-6: J43.A7, J43.B7, J44.5
USB_D-7: J50.A7, J50.B7, J51.5
VIN: BYP.2, C1.1, C2.+, C13.1, D3.C, F2.2, J15.9, R5.2, U5.8
VIN1: BYP1.2, C5.1, C6.1, C7.+, D8.C, F1.2, J8.9, R9.2, U2.8
VIN2: BYP2.2, C17.1, C18.1, C19.+, D13.C, F3.2, J16.9, R16.2, U4.8
VIN3: BYP3.2, C25.1, C26.1, C27.+, D18.C, F4.2, J23.9, R22.2, U7.8
VIN4: BYP4.2, C33.1, C34.1, C35.+, D23.C, F5.2, J30.9, R28.2, U9.8
VIN5: BYP5.2, C41.1, C42.1, C43.+, D28.C, F6.2, J37.9, R34.2, U11.8
VIN6: BYP6.2, C49.1, C50.1, C51.+, D33.C, F7.2, J44.9, R40.2, U13.8
VIN7: BYP7.2, C57.1, C58.1, C59.+, D38.C, F8.2, J51.9, R46.2, U15.8
VREG_EN: D1.C, JP6.2, R5.1, U5.5
VREG_EN1: D7.C, JP2.2, R9.1, U2.5
VREG_EN2: D12.C, JP5.2, R16.1, U4.5
VREG_EN3: D17.C, JP8.2, R22.1, U7.5
VREG_EN4: D22.C, JP10.2, R28.1, U9.5
VREG_EN5: D27.C, JP12.2, R34.1, U11.5
VREG_EN6: D32.C, JP14.2, R40.1, U13.5
VREG_EN7: D37.C, JP16.2, R46.1, U15.5
V_BATT: C3.1, D3.A, J3.2, J4.1, U1.3
V_BATT1: C15.1, D8.A, J10.2, J11.1, U3.3
V_BATT2: C23.1, D13.A, J18.2, J19.1, U6.3
V_BATT3: C31.1, D18.A, J25.2, J26.1, U8.3
V_BATT4: C39.1, D23.A, J32.2, J33.1, U10.3
V_BATT5: C47.1, D28.A, J39.2, J40.1, U12.3
V_BATT6: C55.1, D33.A, J46.2, J47.1, U14.3
V_BATT7: C63.1, D38.A, J53.2, J54.1, U16.3
V_USB: C4.1, D4.A, D5.A, J1.VBUS1, J1.VBUS2, U1.4
V_USB1: C16.1, D9.A, D10.A, J7.VBUS1, J7.VBUS2, U3.4
V_USB2: C24.1, D14.A, D15.A, J14.VBUS1, J14.VBUS2, U6.4
V_USB3: C32.1, D19.A, D20.A, J22.VBUS1, J22.VBUS2, U8.4
V_USB4: C40.1, D24.A, D25.A, J29.VBUS1, J29.VBUS2, U10.4
V_USB5: C48.1, D29.A, D30.A, J36.VBUS1, J36.VBUS2, U12.4
V_USB6: C56.1, D34.A, D35.A, J43.VBUS1, J43.VBUS2, U14.4
V_USB7: C64.1, D39.A, D40.A, J50.VBUS1, J50.VBUS2, U16.4
V_USB_1: BYP1.1, D10.C, F1.1
V_USB_2: BYP.1, D5.C, F2.1
V_USB_3: BYP2.1, D15.C, F3.1
V_USB_4: BYP3.1, D20.C, F4.1
V_USB_5: BYP4.1, D25.C, F5.1
V_USB_6: BYP5.1, D30.C, F6.1
V_USB_7: BYP6.1, D35.C, F7.1
V_USB_8: BYP7.1, D40.C, F8.1

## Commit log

2020-11-30 Create Eagle files
2020-11-30 Preliminary schematic done?
2020-12-01 Board layout
2020-12-02 Layout
2020-12-02 Created part for stand off, proto layout finished
2020-12-02 Switch out stand offs
2020-12-03 Create 2x1 version and generate production files
2020-12-03 Renamed from qwiic snap to qwiic carrier
2020-12-07 Remove production files. Design review changes
2020-12-08 Fix silk screen
2020-12-08 Checklist
2020-12-08 Review before ordering
2020-12-09 silkscreen
2020-12-09 silk screen
2020-12-10 Update measures on 2x1
2020-12-10 Silk screen changes
2020-12-11 QC Feedback
2020-12-15 Generate CAM files
2021-01-18 Update tcream for 4-40 standoffs
2021-01-18 Run of engineering checklist
2021-01-19 Changes from design review
2021-01-20 Add dimensions to 2x1
2021-01-21 Silk changes from red board design review
2021-01-21 Remove redundant production files
    Accidentally tried to panelize a panel
2021-01-21 Move SF logo, board name silk screen on bottom
    Renamed eagle files from 1x1, 2x1 to single, double
    Cleaned up library files
2021-01-22 Panelized both 1x1 and 2x1
2021-01-22 Renaming
    1x1 --> Single
    2x1 --> Double
    Re-panelized
2021-01-22 Re-panelized with corrected position silk screen
    This is the last time I've got to re-panel hopefully!
2021-01-22 Add eagle files to .zip folder
2021-03-18 Update README.md
    Update documentation links
2021-03-18 Update README.md
    Remove unused bullet points

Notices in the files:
parts and their libraries:
SparkFun-Aesthetics: Licensing: Creative Commons ShareAlike 4.0 International - https://creativecommons.org/licenses/by-sa/4.0
SparkFun-Aesthetics: Released under the Creative Commons Attribution Share-Alike 4.0 License
SparkFun-Aesthetics: https://creativecommons.org/licenses/by-sa/4.0
